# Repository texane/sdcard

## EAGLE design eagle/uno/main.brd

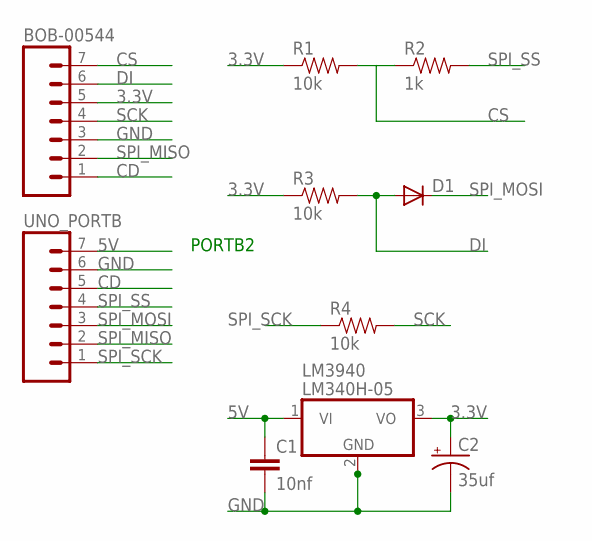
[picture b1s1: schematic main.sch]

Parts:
BOB-00544: M07; 1X07
C1: 10nf; CAP-PTH-SMALL
C2: 35uf; CPOL-RADIAL-100UF-25V
D1: DIODE1N4148; DIODE-1N4148
LM3940: LM340H-05; TO220H
R1, R3, R4: 10k; AXIAL-0.4
R2: 1k; AXIAL-0.4
UNO_PORTB: M07; 1X07

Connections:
3.3V: BOB-00544.5, C2.1 (+), LM3940.3 (VO), R1.P$1 (1), R3.P$1 (1)
5V: C1.1, LM3940.1 (VI), UNO_PORTB.7
CD: BOB-00544.1, UNO_PORTB.5
CS: BOB-00544.7, R1.P$2 (2), R2.P$1 (1)
DI: BOB-00544.6, D1.A, R3.P$2 (2)
GND: BOB-00544.3, C1.2, C2.2 (-), LM3940.2 (GND), UNO_PORTB.6
SCK: BOB-00544.4, R4.P$2 (2)
SPI_MISO: BOB-00544.2, UNO_PORTB.2
SPI_MOSI: D1.C, UNO_PORTB.3
SPI_SCK: R4.P$1 (1), UNO_PORTB.1
SPI_SS: R2.P$2 (2), UNO_PORTB.4

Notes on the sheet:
PORTB2

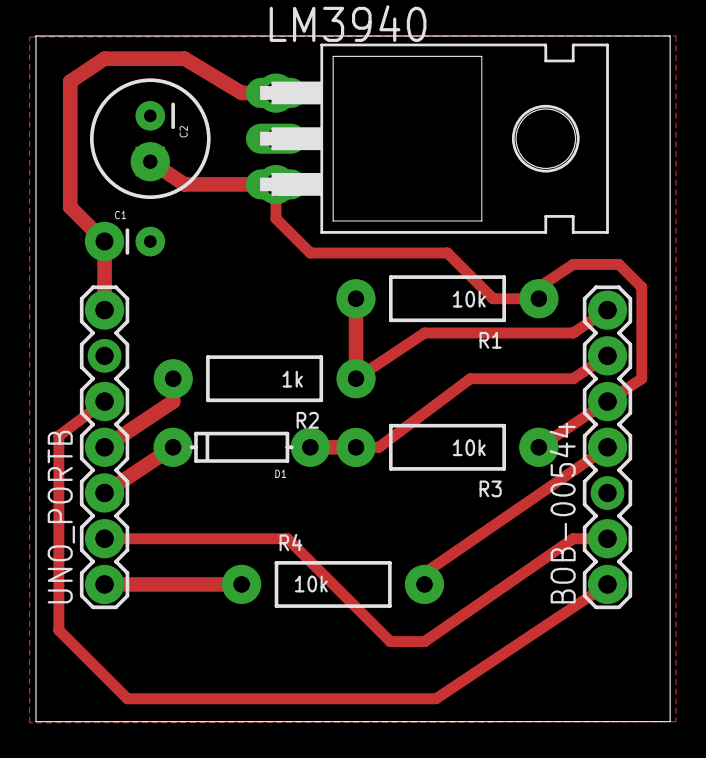
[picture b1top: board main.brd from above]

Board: 2 copper layers, 35.2 x 38.1 mm, 10 parts (0 on the bottom side), 11 nets.

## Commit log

2012-08-19 [ add ] src
2012-08-19 [ wip ]
2012-08-19 [ add ] doc/notes
2012-08-20 [wip] initialization sequence compile, to be tested
2012-08-20 [ fix ] sd_read_r3
2012-08-20 [ todo ]
2012-08-20 [ update ] doc, atmega328 type sizes ref
2012-08-20 [ update ] add regtype_t
2012-08-20 [wip] initialization sequence tested, working.
2012-08-20 [ update ] read_csd, wip
2012-08-21 [ update ] sd_print_csd
2012-08-21 [ update ] spi_read_512
2012-08-21 [ update ] CONFIG_SIZEOF_REGTYPE
2012-08-21 [ update ] sd_read_block, sd_write_block, sd_erase. to be tested.
2012-08-21 [ update ] minor
2012-08-21 [ update ] unused CSD commands
2012-08-21 [ update ] doc/notes, todo
2012-08-21 [ fix ] sd_write_block, replace acmd13 with cmd13. missing dummy crc.
2012-08-21 [ fix ] missing const qualifiers
2012-08-21 [ update ] remove sd_make_cmd, use sd_write_cmd
2012-08-21 [ update ] comments
2012-08-21 [ update ] s/sd_cmd_buf/sd_resp_buf/
2012-08-21 [ add ] eagle uno board
2012-08-21 [ add ] eagle/uno board, add larger via
2012-08-21 [ add ] eagle/uno, main.png
2012-08-21 [ update ] eagle/uno, rotate sdcard board connector
2012-08-21 [ update ] eagle/uno, printed version
2012-08-21 [ update ] src, remove main delay loop, add sd_{read,write}_block tests
2012-08-22 [ update ] sd_set_sck_freq
2012-08-22 [ update ] spi_set_sck_freq
2012-08-24 [ fix ] eagle/uno, voltage regulator footprint (TO220)
2012-08-26 [ update ] conditionnal debugging
2012-08-26 [ fix ] small delay needed in spi_write_uint8 for sd_read_block
2012-08-26 [ fix ] add sd_read_block FIXME

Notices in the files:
parts and their libraries:
SparkFun: Licensing: CC v3.0 Share-Alike You are welcome to use this library for commercial purposes.
